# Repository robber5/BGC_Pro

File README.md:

# Flying5_BGC
A Brushless Gimbal Controller, design for GoPro and Quadcopter.

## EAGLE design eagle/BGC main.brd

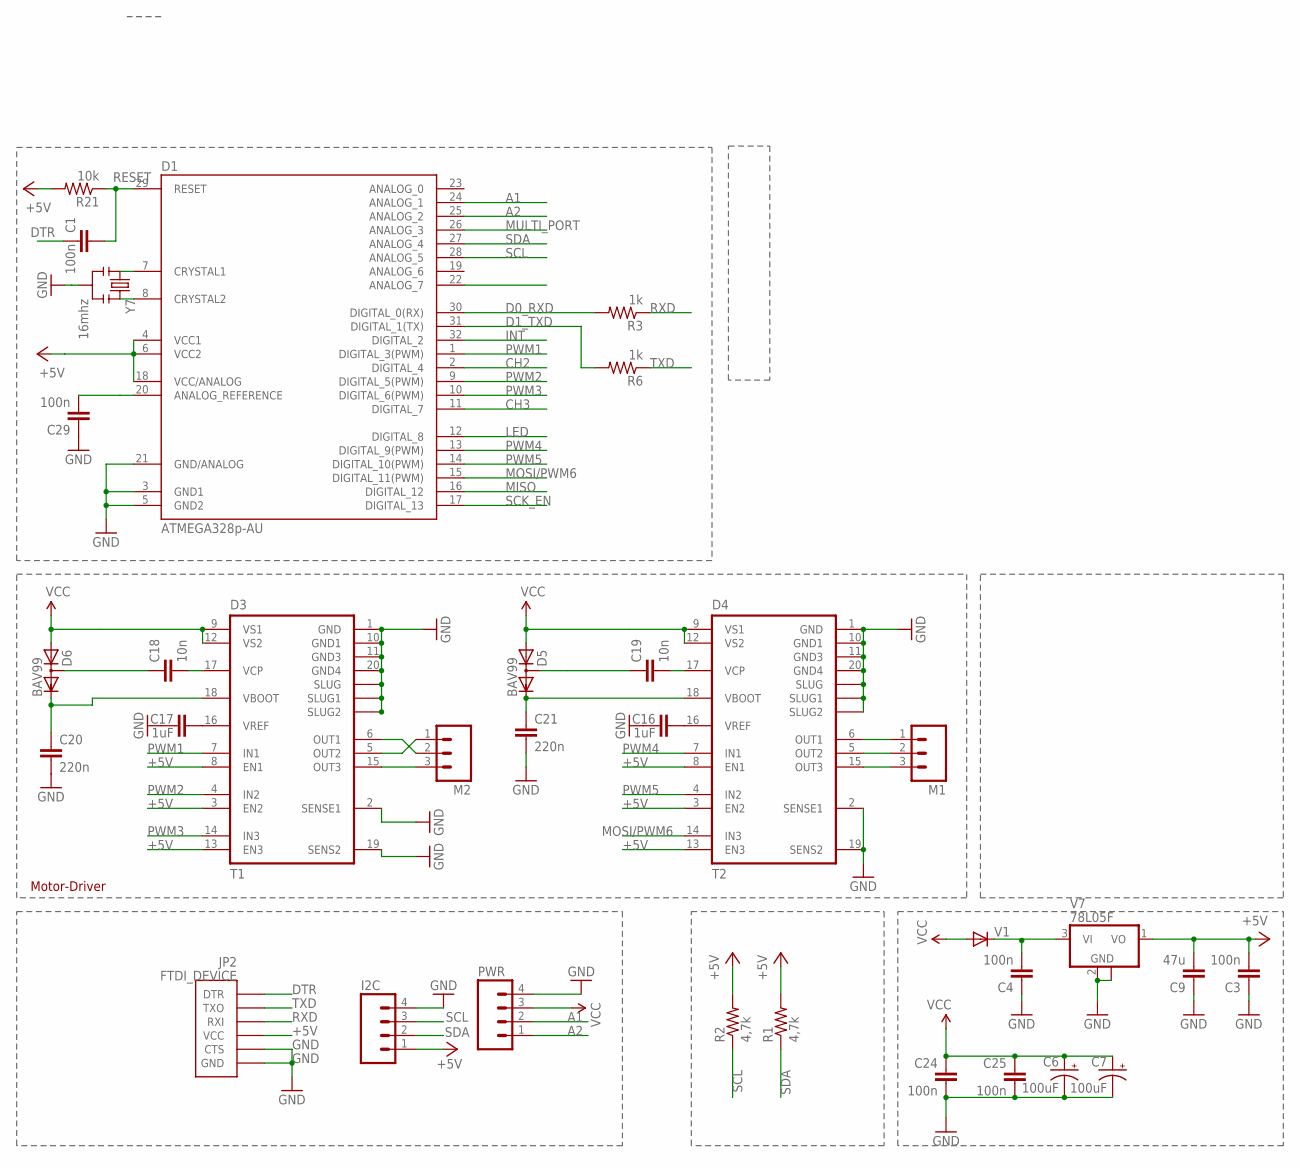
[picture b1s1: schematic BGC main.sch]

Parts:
C1, C3, C4, C24, C25, C29: 100n; 0402-CAP
C6, C7: 100uF; EIA7343
C9: 47u; C1210
C16, C17: 1uF; 0402-CAP
C18, C19: 10n; 0402-CAP
C20, C21: 220n; 0402-CAP
D1: ATMEGA328p-AU; TQFP32-08
D3: T1; SO20POWER2
D4: T2; SO20POWER2
D5, D6: BAV99; SOT23
I2C: M04PTH; 1X04
JP2: FTDI_DEVICE; FTDI_DEVICE_SIDE
M1, M2: M03PTH; 1X03
PWR: M04PTH; 1X04
R1, R2: 4,7k; 0402-RES
R3, R6: 1k; 0402-RES
R21: 10k; 0402-RES
V1: DIODE-DO214AC; DO214AC
V7: 78L05F; SOT89
Y7: 16mhz; RESONATOR-SMD

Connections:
+5V: C3.2, C9.2, D1.4 (VCC1), D1.6 (VCC2), D1.18 (VCC/ANALOG), D3.3 (EN2), D3.8 (EN1), D3.13 (EN3), D4.3 (EN2), D4.8 (EN1), D4.13 (EN3), I2C.1, JP2.P$4 (VCC), R1.2, R2.2, R21.2, V7.1 (VO)
A1: D1.24 (ANALOG_1), PWR.2
A2: D1.25 (ANALOG_2), PWR.1
A7: D1.22 (ANALOG_7)
CH2: D1.2 (DIGITAL_4)
CH3: D1.11 (DIGITAL_7)
D0_RXD: D1.30 (DIGITAL_0(RX)), R3.2
D1_TXD: D1.31 (DIGITAL_1(TX)), R6.2
DTR: C1.1, JP2.P$1 (DTR)
GND: C3.1, C4.1, C6.C (-), C7.C (-), C9.1, C16.1, C17.1, C20.2, C21.2, C24.2, C25.2, C29.1, D1.3 (GND1), D1.5 (GND2), D1.21 (GND/ANALOG), D3.1 (GND), D3.2 (SENSE1), D3.10 (GND1), D3.11 (GND3), D3.19 (SENS2), D3.20 (GND4), D3.SLUG (SLUG1), D3.SLUG1 (SLUG2), D3.SLUG2 (SLUG), D4.1 (GND), D4.2 (SENSE1), D4.10 (GND1), D4.11 (GND3), D4.19 (SENS2), D4.20 (GND4), D4.SLUG (SLUG1), D4.SLUG1 (SLUG2), D4.SLUG2 (SLUG), I2C.4, JP2.P$5 (CTS), JP2.P$6 (GND), PWR.4, V7.2 (GND), V7.2@1 (GND), Y7.2
INT: D1.32 (DIGITAL_2)
LED: D1.12 (DIGITAL_8)
MISO: D1.16 (DIGITAL_12)
MOSI/PWM6: D1.15 (DIGITAL_11(PWM)), D4.14 (IN3)
MULTI_PORT: D1.26 (ANALOG_3)
unnamed: C16.2, D4.16 (VREF)
unnamed: C17.2, D3.16 (VREF)
unnamed: C18.2, D3.17 (VCP)
unnamed: C19.2, D4.17 (VCP)
unnamed: C19.1, D5.3 (AC)
unnamed: C21.1, D4.18 (VBOOT), D5.2 (C)
unnamed: D3.15 (OUT3), M2.3
unnamed: D4.6 (OUT1), M1.1
unnamed: D4.5 (OUT2), M1.2
unnamed: D4.15 (OUT3), M1.3
unnamed: D3.5 (OUT2), M2.1
unnamed: D3.6 (OUT1), M2.2
unnamed: D1.8 (CRYSTAL2), Y7.3
unnamed: D1.7 (CRYSTAL1), Y7.1
unnamed: C29.2, D1.20 (ANALOG_REFERENCE)
PWM1: D1.1 (DIGITAL_3(PWM)), D3.7 (IN1)
PWM2: D1.9 (DIGITAL_5(PWM)), D3.4 (IN2)
PWM3: D1.10 (DIGITAL_6(PWM)), D3.14 (IN3)
PWM4: D1.13 (DIGITAL_9(PWM)), D4.7 (IN1)
PWM5: D1.14 (DIGITAL_10(PWM)), D4.4 (IN2)
RESET: C1.2, D1.29 (RESET), R21.1
RXD: JP2.P$3 (RXI), R3.1
SCK_EN: D1.17 (DIGITAL_13)
SCL: D1.28 (ANALOG_5), I2C.3, R2.1
SDA: D1.27 (ANALOG_4), I2C.2, R1.1
TXD: JP2.P$2 (TXO), R6.1
VBOOT1: C20.1, D3.18 (VBOOT), D6.2 (C)
VCC: C6.A (+), C7.A (+), C24.1, C25.1, D3.9 (VS1), D3.12 (VS2), D4.9 (VS1), D4.12 (VS2), D5.1 (A), D6.1 (A), PWR.3, V1.A
VCC_VI: C4.2, V1.C, V7.3 (VI)
VCP1: C18.1, D6.3 (AC)

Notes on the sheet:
Motor-Driver

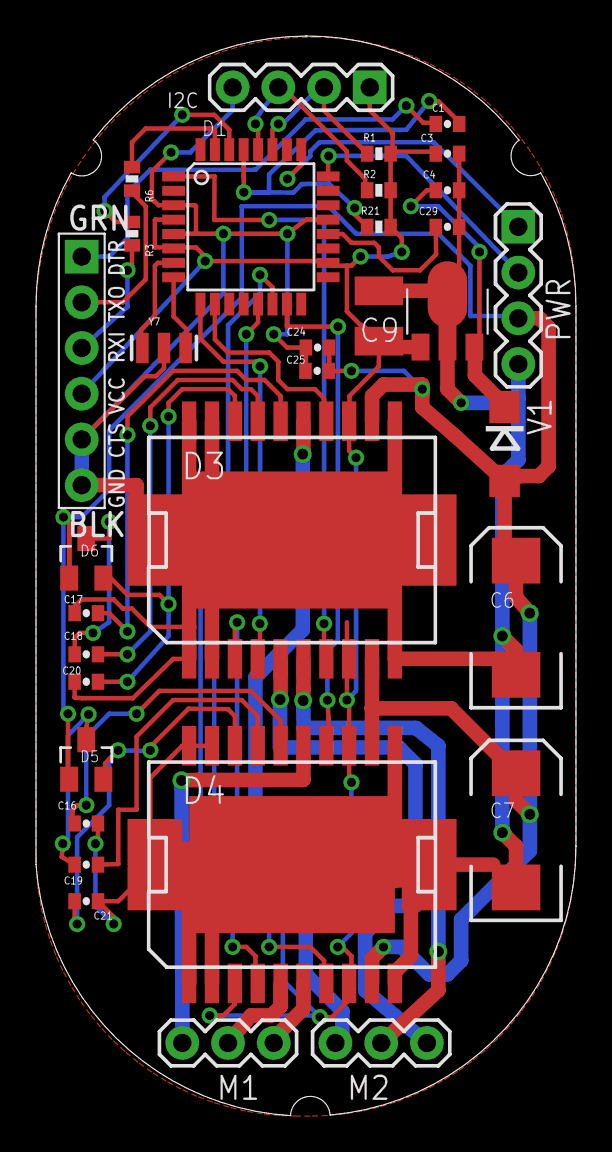
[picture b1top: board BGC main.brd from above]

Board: 2 copper layers, 30.0 x 60.0 mm, 33 parts (0 on the bottom side), 37 nets.

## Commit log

2015-09-18 images upload
2015-09-19 eagle upload
2015-10-11 3Dmodel

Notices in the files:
parts and their libraries:
SparkFun-Capacitors: Licensing: Creative Commons ShareAlike 4.0 International - https://creativecommons.org/licenses/by-sa/4.0
